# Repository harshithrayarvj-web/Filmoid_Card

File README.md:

# Filmoid_Card
A small card like device meant to resemble instant film and contains an LED matrix.

This device is meant to show sensor data, making it easier to know about certain data when needed, such as temperature or acceleration, while also using the LED matrix for fun with animations and maybe as a weak flashlight.
It is planned to have it be a device that can be compact while also reading sensor data from the humidity/temperature sensor and the IMU. Use cases for this could be things such as tracking plants, or measuring inertial measurements while displaying them on the led matrix. The size and compactness of this device should make it easy to produce, especially if they need to be cheap, such as for measuring plants, and also need something like a xiao for processing that data (as an input device or it's own device that can do actions using data from the sensors).

Although this is compact, with a next revision I could rework the pcb to contain the mcu right on the board to make it more compact and reduce costs, while also improving it's capability, like adding the IMU right on the pcb and adding more sensors. This way I can reduce costs and make it more compact, and potentially make it very compact that it can be a small and cheap addition for small projects like potted plant gardens or as a sensor module for a larger project. Hopefully a wireless version could be possible. I can't promise a revision, but if it is going to be real, then I would rename this and give it to a different project that would benefit more.

|          Name         | Amount | Unit | Total |    Vendor   | Funding   |
|:---------------------:|:------:|:----:|:-----:|:-----------:|-----------|
| 0603 Yellow LED SMD   | 30     | 0.1  | 3     | Digikey     | 30        |
| MPU6050               | 1      | 8.59 | 8.59  | Amazon      | Left Over |
| 10k SMD 0603 resistor | 1      | 0.1  | 0.1   | Digikey     | 11.26     |
| XIAO RP2040 MCU       | 1      | 4.9  | 4.9   | Digikey     |           |
| DHT11                 | 1      | 1.89 | 1.89  | Ali Express |           |
| Switch                | 2      | 0.13 | 0.26  | Digikey     |           |
| PCB(selffunded)       | 1      | 4    | 30.64 | JLCPCB      |           |
|                       |        |      | 49.38 |             |           |

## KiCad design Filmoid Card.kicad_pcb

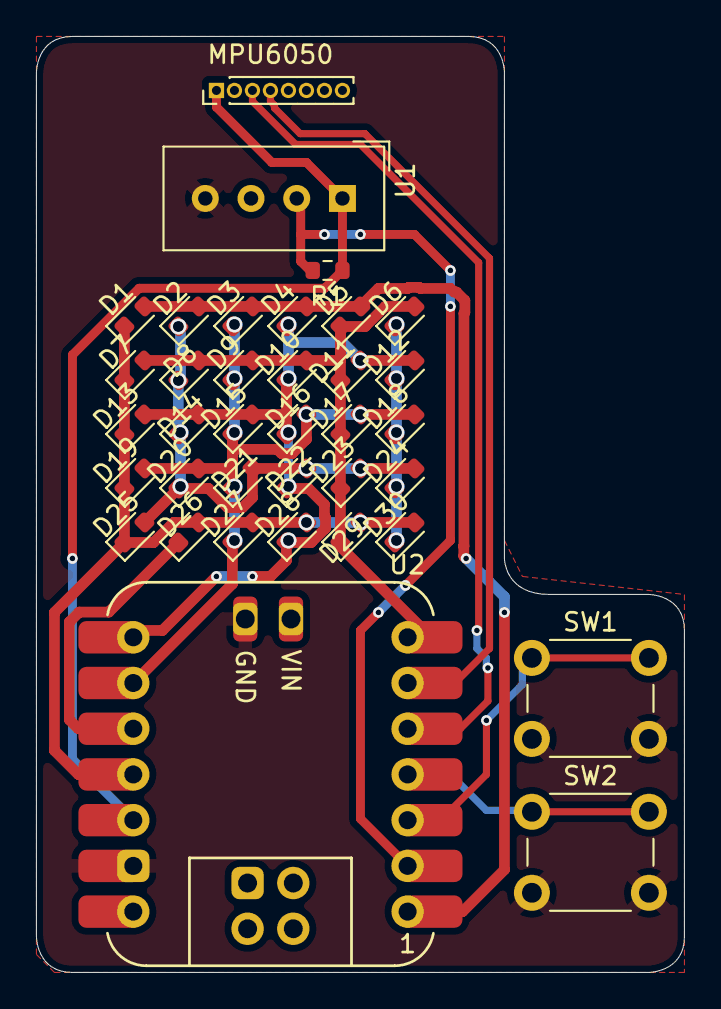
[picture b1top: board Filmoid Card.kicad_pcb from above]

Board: 2 copper layers, 36.0 x 52.0 mm, 36 parts (0 on the bottom side), 14 nets.

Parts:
D1, D2, D3, D4, D5, D6, D7, D8, D9, D10, D11, D12, D13, D14, D15, D16, D17, D18, D19, D20, D21, D22, D23, D24, D25, D26, D27, D28, D29, D30: LED_45deg; LED_0603_1608Metric
MPU6050: Conn_01x08_Pin; PinHeader_1x08_P1.00mm_Vertical
R1: 10k; R_0603_1608Metric
SW1, SW2: SW_Push; SW_PUSH_6mm_H5mm
U1: DHT11; Aosong_DHT11_5.5x12.0_P2.54mm
U2: Seeeduino Xiao rp2040; Xiao_rp2040_ACH

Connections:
+3.3V: MPU6050.1, R1.1, U1.1 (VDD), U2.10 (3V3)
/DHT11 data: R1.2, U1.2 (DATA), U2.2 (P27)
/Plex1: D1.2 (A), D2.2 (A), D3.2 (A), D4.2 (A), D5.2 (A), U2.1 (P26)
/Plex2: D5.1 (K), D6.2 (A), D7.2 (A), D8.2 (A), D9.2 (A), D10.2 (A), D11.1 (K), D17.1 (K), D23.1 (K), D29.1 (K), U2.7 (P0)
/Plex3: D4.1 (K), D10.1 (K), D11.2 (A), D12.2 (A), D13.2 (A), D14.2 (A), D15.2 (A), D16.1 (K), D22.1 (K), D28.1 (K), U2.14 (P1)
/Plex4: D3.1 (K), D9.1 (K), D15.1 (K), D16.2 (A), D17.2 (A), D18.2 (A), D19.2 (A), D20.2 (A), D21.1 (K), D27.1 (K), U2.13 (P2)
/Plex5: D2.1 (K), D8.1 (K), D14.1 (K), D20.1 (K), D21.2 (A), D22.2 (A), D23.2 (A), D24.2 (A), D25.2 (A), D26.1 (K), U2.12 (P4)
/Plex6: D1.1 (K), D7.1 (K), D13.1 (K), D19.1 (K), D25.1 (K), D26.2 (A), D27.2 (A), D28.2 (A), D29.2 (A), D30.2 (A), U2.11 (P3)
/SCL: MPU6050.3, U2.5 (P6)
/SDA: MPU6050.4, U2.6 (P7)
/SW1: SW1.1, U2.3 (P28)
/SW2: SW2.1, U2.4 (P29)
GND: MPU6050.2, SW1.2, SW2.2, U1.4 (GND), U2.9 (GND), U2.18 (GND)
unnamed: D6.1 (K), D12.1 (K), D18.1 (K), D24.1 (K), D30.1 (K)
